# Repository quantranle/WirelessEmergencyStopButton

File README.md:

# Wireless Emergency Stop Button

by: Le Minh Quan Tran / Pham Duc Binh

**Faculty of Technology and Bionics**

***Rhine-Waal University of Applied Sciences***

Date: 13 January 2025

----

## Abstract

This project presents the design and implementation of a Wireless Emergency Stop Button (WESB)
 for enhancing safety in IoT applications, specifically the E-Go-Cart. 
 The WESB utilizes an ESP8266-based wireless communication link operating on a Wi-Fi network. 
 A mechanical button on the transmitter triggers an emergency stop signal, which is then transmitted 
 wirelessly to the receiver. The receiver is connected to the E-Go-Cart via a digital input/output interface. 
 Upon receiving the stop signal, the receiver initiates an emergency braking sequence implemented using MATLAB/Simulink, 
 bringing the E-Go-Cart to a safe halt within a defined distance. This system provides a reliable and efficient means 
 for remote emergency control of electric vehicles, improving overall safety and operational reliability.

## Table of Contents

[[_TOC_]]

## 1 Introduction

The increasing prevalence of electric vehicles (EVs), including those used in educational and recreational settings, 
demands robust safety mechanisms. This project addresses the need for a reliable and efficient emergency stop system for EVs,
 drawing inspiration from a real-world incident at Rhine-Waal University.

During a student festival, students were driving E-Go-Cart around campus under supervision. An accident occurred when a student, 
experiencing panic, lost control of their vehicle, potentially endangering pedestrians. Although the E-Go-Cart was equipped with 
an emergency stop button, the student's panicked state hindered their ability to react effectively. This incident underscored 
the limitations of traditional emergency stop mechanisms in high-stress situations and emphasized the need for a more robust and accessible solution.

Compared to traditional on-board emergency stop buttons, the WESB offers several advantages:

- Reduced Stress: Remote control eliminates the need for panicked individuals to locate and activate a specific button on the vehicle.
- Enhanced Accessibility: Integration with mobile applications provides convenient access to the emergency stop function.
- Centralized Control: The WESB allows for the simultaneous control of multiple vehicles, making it ideal for managing fleets or large-scale events.

This project seeks to address the shortcomings of existing safety measures and provide a more 
reliable and effective solution for ensuring the safe operation of electric vehicles in diverse settings.

## 2	Bill of Materials
| No. | Quality | Manufacturer               | Component               | Ordering code (manufacturer) | Vendor | Ordering code (vendor) | Price per unit (€) | Price (€)|
|:---:| :---:   | :---:                      | :---:                   | :---:                        | :---:  | :---:                  | :---:              | :---:    |
| 1   | 2       |                            | 2 AA cell holder        |                              | HSRW   |                        |                    |          |
| 2   | 1       |                            | PUSH BUTTON             |                              | HSRW   |                        |                    |          |
| 3   | 1       |                            | BUZZER                  |                              | HSRW   |                        |                    |          |
| 4   | 1       |                            | RED LED                 |                              | HSRW   |                        |                    |          |
| 5   | 1       |                            | GREEN LED               |                              | HSRW   |                        |                    |          |
| 6   | 1       |                            | POWER SWITCH            |                              | HSRW   |                        |                    |          |
| 7   | 1       | Diptronics                 | RESET BUTTON            |  DTSMF-32N-V-T/R             | Mouser | 113-DTSMF32NVTR        | 0.41               | 0.41     |
| 8   | 1       | Joy-IT                     | ESP8266                 | ESP8266-12F                  | Conrad | 1707668 - NA           | 4.19               | 4.19     |
| 9   | 1       | Semtech                    | RF Transceiver          | SX1268IMLTRT                 | Mouser | 947-SX1268IMLTRT       | 3.85               | 3.85     |
| 10  | 1       | Maxlinear                  | Voltage regulator       | SPX1117M3-L-3-3/TR           | Mouser | 701-SPX1117M3-L-33TR   | 0.49               | 0.49     |
| 11  | 1       | Silicon Laboratories       | USB Controller          | CP2102N-A02-GQFN28           | Mouser | 634-CP2102NA02GQFN28   | 3.28               | 3.28     |
| 12  | 1       | GlobalConnector Technology | Micro-usb header        | USB3140-30-0170-0-C          | Mouser | 640-USB31403001700C    | 0.75               | 0.75     |
| 13  | 1       | LPRS                       | RF Connector            | SMA CONNECTOR                | Mouser | 471-SMACONNECTOR       | 2.03               | 2.03     |
| 14  | 1       | Murata                     | RF Inductors - L1       | LQG15HS56NJ02D               | Mouser | 81-LQG15HS56NJ02D      | 0.09               | 0.09     |
| 15  | 1       | Murata                     | RF Inductors - L2       | LQG15HS8N2J02D               | Mouser | 81-LQG15HS8N2J02D      | 0.09               | 0.09     |
| 16  | 1       | Murata                     | RF Inductors - L3       | LQG15HN18NJ02D               | Mouser | 81-LQG15HN18NJ02D      | 0.09               | 0.09     |
| 17  | 1       | Murata                     | RF Inductors - L4       | LQW15AN33NH00D               | Mouser | 81-LQW15AN33NH00D      | 0.14               | 0.14     |
| 18  | 1       | TDK                        | Power Inductors - L5    | MLZ2012M150WT000             | Mouser | 810-MLZ2012M150WT000   | 0.11               | 0.11     |
| 19  | 1       | NDK                        | Crystals - Y1           | NX2016SA-32M-EXS00A-CS06465  | Mouser | 344-NX2016SA32S06465   | 0.52               | 0.52     |
| 20  | 1       |                            | Ceramic Capacitor - C1  |                              | HSRW   |                        |                    |          |
| 21  | 1       | KEMET                      | Ceramic Capacitor - C2  | C1206C475M4RACTU             | Mouser | 80-C1206C475M4R        | 0.88               | 0.88     | 
| 22  | 1       | KEMET                      | Ceramic Capacitor - C3  | C1206C475M4RACTU             | Mouser | 80-C1206C475M4R        | 0.88               | 0.88     | 
| 23  | 1       |                            | Ceramic Capacitor - C4  |                              | HSRW   |                        |                    |          | 
| 24  | 1       | KEMET                      | Ceramic Capacitor - C5  | C1206C475M4RACTU             | Mouser | 80-C1206C475M4R        | 0.88               | 0.88     |
| 25  | 1       |                            | Ceramic Capacitor - C6  |                              | HSRW   |                        |                    |          |
| 26  | 1       | Murata                     | Ceramic Capacitor - C7  | GRM155R71A474KE01D           | Mouser | 81-GRM155R71A474KE1D   | 0.36               | 0.36     |
| 27  | 1       | Murata                     | Ceramic Capacitor - C8  | GRM155R71C473KA01D           | Mouser | 81-GRM155R71C473KA01   | 0.09               | 0.09     |
| 28  | 1       | Murata                     | Ceramic Capacitor - C9  | GCM1555C1H820JA16D           | Mouser | 81-GCM1555C1H820JA6D   | 0.09               | 0.09     |
| 29  | 1       | Murata                     | Ceramic Capacitor - C10 | GJM1555C1H120JB01D           | Mouser | 81-GJM1555C1H120JB1D   | 0.12               | 0.12     |
| 30  | 1       | Murata                     | Ceramic Capacitor - C11 | GJM1555C1H3R6CB01D           | Mouser | 81-GJM1555C1H3R6CB1D   | 0.09               | 0.09     |
| 31  | 1       | Murata                     | Ceramic Capacitor - C12 | GJM1555C1H120JB01D           | Mouser | 81-GJM1555C1H120JB1D   | 0.12               | 0.12     |
| 32  | 1       | Murata                     | Ceramic Capacitor - C13 | GCM1555C1H101JA16D           | Mouser | 81-GCM1555C1H101JA6D   | 0.09               | 0.09     |
| 33  | 1       | Murata                     | Ceramic Capacitor - C14 | GJM1555C1H8R2CB01D           | Mouser | 81-GJM1555C1H8R2CB01   | 0.09               | 0.09     |
| 34  | 1       | Murata                     | Ceramic Capacitor - C15 | GJM1555C1H4R7CB01D           | Mouser | 81-GJM1555C1H4R7CB1D   | 0.09               | 0.09     |
| 35  | 1       | Murata                     | Ceramic Capacitor - C16 | GJM1555C1H3R9CB01D           | Mouser | 81-GJM1555C1H3R9CB1D   | 0.09               | 0.09     |
| 36  | 1       | Murata                     | Ceramic Capacitor - C17 | GJM1555C1H1R0BB01D           | Mouser | 81-GJM1555C1H1R0BB01   | 0.09               | 0.09     |
| 37  | 1       | Murata                     | Ceramic Capacitor - C18 | GCM1555C1H101JA16D           | Mouser | 81-GCM1555C1H101JA6D   | 0.09               | 0.09     |
| 38  | 1       | Murata                     | Ceramic Capacitor - C19 | GJM1555C1H120JB01D           | Mouser | 81-GJM1555C1H120JB1D   | 0.12               | 0.12     |
| 39  | 1       | Murata                     | Ceramic Capacitor - C20 | GJM1555C1H120JB01D           | Mouser | 81-GJM1555C1H120JB1D   | 0.12               | 0.12     |
| 40  | 3       | Littelfuse                 | TVS Diodes              | SP0503BAHTG                  | Mouser | 576-SP0503BAHTG        | 0.65               | 1.95     |
| 41  | 1       |                            | Resistor - R1           |                              | HSRW   |                        |                    |          |
| 42  | 1       |                            | Resistor - R2           |                              | HSRW   |                        |                    |          |
| 43  | 1       |                            | Resistor - R2           |                              | HSRW   |                        |                    |          |
| 44  | 1       |                            | Resistor - R4           |                              | HSRW   |                        |                    |          |
| 45  | 1       |                            | Resistor - R5           |                              | HSRW   |                        |                    |          |
| 46  | 1       |                            | Resistor - R6           |                              | HSRW   |                        |                    |          |
| 47  | 1       |                            | Resistor - R7           |                              | HSRW   |                        |                    |          |
| 48  | 1       |                            | Resistor - R8           |                              | HSRW   |                        |                    |          |
| 49  | 1       |                            | Resistor - R9           |                              | HSRW   |                        |                    |          |
| 50  | 1       |                            | Resistor - R10          |                              | HSRW   |                        |                    |          |
| 51  | 1       | Vishay                     | Resistor - R11          | CRCW04020000Z0ED             | Mouser | 71-CRCW0402-0-E3       | 0.09               | 0.09     |
| 52  | 2       |                            | 1x02 PIN HEADER         |                              | HSRW   |                        |                    |          |
| 53  | 2       |                            | 1x08 PIN HEADER         |                              | HSRW   |                        |                    |          |

## 3	Methodology

### 3.1     Schematic
Final Schematic:

 Figure 1: Schematic

### 3.2     PCB Design
Final PCB:

 Figure 2: PCB design

### 3.3     Prototyping

### 3.4     Assembly Process

#### 3.4.1 Soldering SMD components
First step: Use a stencil and apply solder paste to PCB.

 Figure 3: Using a stencil

After applying solder paste, pick up all SMD components and make sure they are all in correct place.

 Figure 4: Put on SMD components

Next, put PCB into the oven then bake it. The setup was supported by Mr. Muh.

 Figure 5: Put PCB into the Oven

 Figure 6: Baking PCB

Last but not least, test the connectivity of the SMD components with the multimeter.

#### 3.4.2 Soldering THT components
Solder THT components with Solder pen.

 Figure 7: Solder THT components

Same as SMD components, make sure all THT components are connected appropriately.

## 4    Programming and uploading firmware
We programmed the ESP8266 chips using Arduino IDE and PlatformIO.  
The files of Transmitter and Receiver are in the ***code/Official code*** folder.

## 5    Troubleshooting
**[1]**
Can power the ESP8266 by USB cable, but not able to program. The device manager from the laptop cannot detect the USB port, although
download a correct driver.

**[2]**
Able to prototype LoRa module, but difficult to implement in the project. There have to be hard-work programming and deep understand in
RF functions.

**[3]**
Able to program the ESP8266 chips by using FDTI FT232RL Module. However, when the ESP8266 chips were soldered to the PCB, we could not
program them by using FDTI module anymore.

## 6	Results
This is the result:
 Figure 8: Final Products

## 7	Power Consumption and Battery Life
**Power Consumption**  
V_supply = 6V (measured)  
I_output = 200mA (measured)  
⇒ P_consumed = V_supply * I_output = 5.5V * 200mA = 1200 mW.  
**P_consumed = 1200 mW**  

**Battery Life**  
Battery capacity of AAA Alkaline: 1200 mAh (datasheet)  
Battery Life = 1200mAh / 200mA = **6 hours**

## 8	Further Improvements
- **Integration with Other Devices:** Integrate wireless e-stops with other E-Carts or Robots to create a comprehensive safety network.
- **Further Program Development:** Sleep mode to optimize the battery life
- **Application of The Lora Module** to increase distance and reliable communication. 
- **Ergonomic Design:** Ensure ergonomic design for comfortable and intuitive operation (Push button, battery level, signal strength,…)

## 9	References

* [1] ESP32 with LoRa using Arduino IDE – Getting Started (https://randomnerdtutorials.com/esp32-lora-rfm95-transceiver-arduino-ide/)
* [2] CP2102N (https://www.mouser.de/datasheet/2/368/cp2102n_datasheet-1634912.pdf)
* [3] ESP-12E WiFi Module (https://components101.com/sites/default/files/2021-09/ESP12E-Datasheet.pdf)
* [4] ESP8266 - Button - Piezo Buzzer (https://newbiely.com/tutorials/esp8266/esp8266-button-piezo-buzzer)
* [5] Configure an ESP8266 as a WiFi Access Point
* [6] CP2102N Driver (https://www.silabs.com/developer-tools/usb-to-uart-bridge-vcp-drivers?tab=overview)
* [7] Best battery for ESP32 (https://diyi0t.com/best-battery-for-esp32-nodemcu/)
* [8] Tips for ESP8266 (https://www.instructables.com/ESP8266-Pro-Tips/)
* [9] Electronic Component Search Engine (https://componentsearchengine.com/)

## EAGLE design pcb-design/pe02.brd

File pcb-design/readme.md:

# PCB design

 Figure 1: ESP8266 PCB design

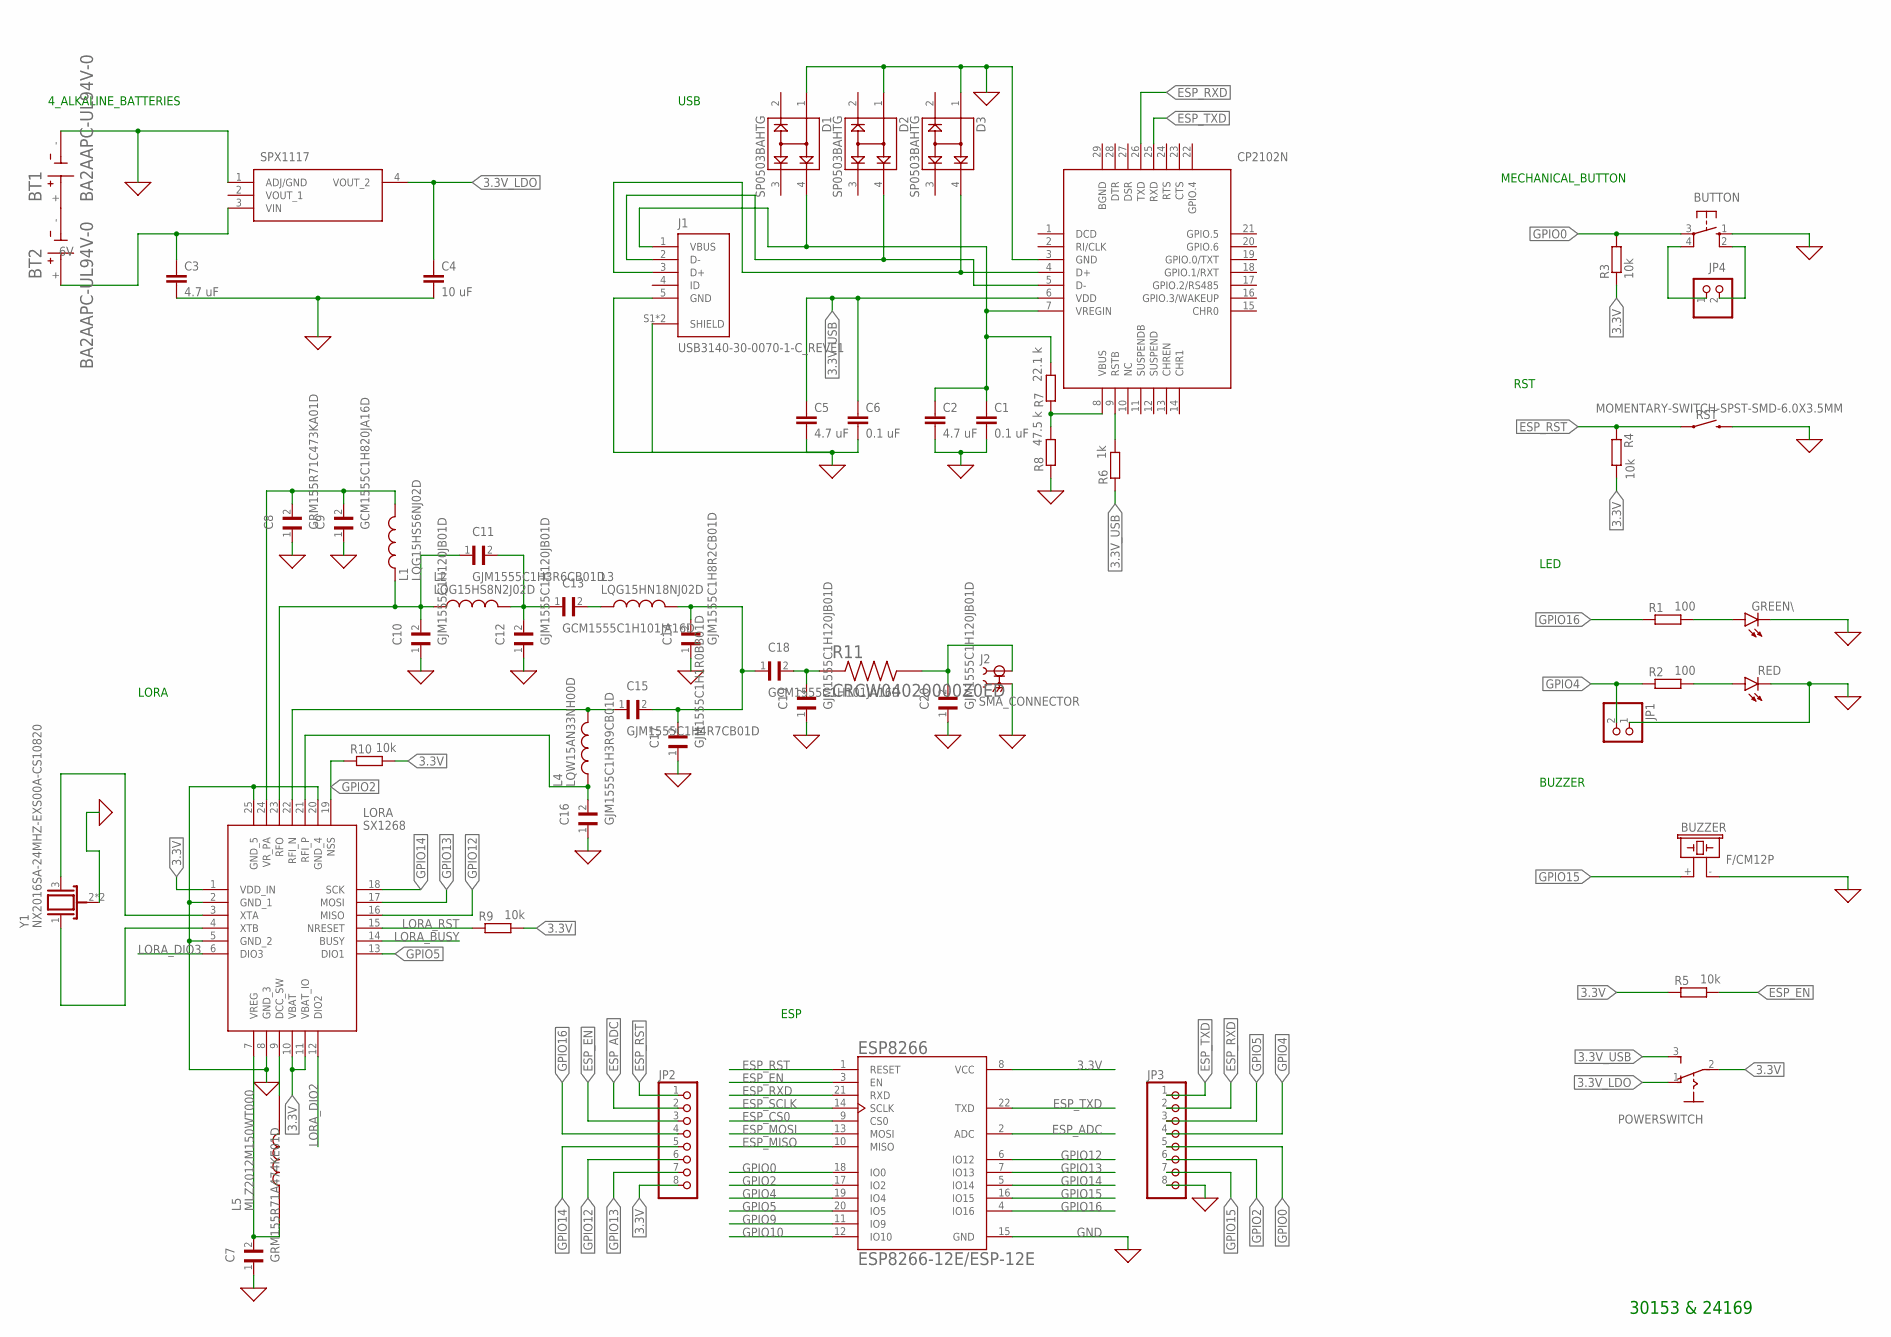
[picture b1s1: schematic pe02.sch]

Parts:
BT1, BT2: BA2AAPC-UL94V-0; BAT_BA2AAPC-UL94V-0
BUTTON: 10-XX; B3F-10XX
BUZZER: F/CM12P
C1, C6: 0.1 uF; C1206K
C2, C3, C5: 4.7 uF; C1206K
C4: 10 uF; C1206K
C7: GRM155R71A474KE01D; CAPC1005X55N
C8: GRM155R71C473KA01D; CAPC1005X55N
C9: GCM1555C1H820JA16D; CAPC1005X55N
C10, C12, C19, C20: GJM1555C1H120JB01D; CAPC1005X55N
C11: GJM1555C1H3R6CB01D; CAPC1005X55N
C13, C18: GCM1555C1H101JA16D; CAPC1005X55N
C14: GJM1555C1H8R2CB01D; CAPC1005X55N
C15: GJM1555C1H4R7CB01D; CAPC1005X55N
C16: GJM1555C1H3R9CB01D; CAPC1005X55N
C17: GJM1555C1H1R0BB01D; CAPC1005X55N
CP2102N: CP2102N-A02-GQFN28; QFN50P500X500X80-29N
D1, D2, D3: SP0503BAHTG; SOT143
ESP8266: ESP8266-12E/ESP-12E; XCVR_ESP8266-12E/ESP-12E
GREEN\: LEDCHIPLED_1206; CHIPLED_1206
J1: USB3140-30-0070-1-C_REVE1; GCT_USB3140-30-0070-1-C_REVE1
J2: SMA_CONNECTOR; LPRS_SMA_CONNECTOR
JP1, JP4: PINHD-1X2; 1X02
JP2, JP3: PINHD-1X8; 1X08
L1: LQG15HS56NJ02D; INDC1005X55N
L2: LQG15HS8N2J02D; INDC1005X55N
L3: LQG15HN18NJ02D; INDC1005X55N
L4: LQW15AN33NH00D; INDC1005X60N
L5: MLZ2012M150WT000; INDC2012X145N
LORA: SX1268; QFN50P400X400X100-25N
POWERSWITCH: 255SB
R1, R2: 100; R1206
R3, R4, R5, R9, R10: 10k; R1206
R6: 1k; R1206
R7: 22.1 k; R1206
R8: 47.5 k; R1206
R11: CRCW04020000Z0ED; RESC1005X40N
RED: LEDCHIPLED_1206; CHIPLED_1206
RST: MOMENTARY-SWITCH-SPST-SMD-6.0X3.5MM; TACTILE_SWITCH_SMD_6.0X3.5MM
SPX1117: SPX1117M3-L-3-3_TR; SOT230P700X180-4N
Y1: NX2016SA-24MHZ-EXS00A-CS10820; OSC_NX2016SA-24MHZ-EXS00A-CS10820

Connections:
3.3V: ESP8266.8 (VCC), JP2.8, LORA.1 (VDD_IN), LORA.10 (VBAT), LORA.11 (VBAT_IO), POWERSWITCH.2, R3.1, R4.2, R5.1, R9.2, R10.2
3.3V_LDO: C4.1, POWERSWITCH.1 (O), SPX1117.4 (VOUT_2)
3.3V_USB: C5.1, C6.1, CP2102N.6 (VDD), POWERSWITCH.3 (S), R6.1
6V: BT2.+, C3.1, SPX1117.3 (VIN)
BGND: CP2102N.29 (BGND)
ESP_ADC: ESP8266.2 (ADC), JP2.2
ESP_CS0: ESP8266.9 (CS0)
ESP_EN: ESP8266.3 (EN), JP2.3, R5.2
ESP_MISO: ESP8266.10 (MISO)
ESP_MOSI: ESP8266.13 (MOSI)
ESP_RST: ESP8266.1 (RESET), JP2.1, R4.1, RST.1
ESP_RXD: CP2102N.26 (TXD), ESP8266.21 (RXD), JP3.2
ESP_SCLK: ESP8266.14 (SCLK)
ESP_TXD: CP2102N.25 (RXD), ESP8266.22 (TXD), JP3.1
GND: BT1.-, BUTTON.1 (S), BUZZER.- (2), C1.2, C2.2, C3.2, C4.2, C5.2, C6.2, C7.1, C8.1, C9.1, C10.1, C12.1, C14.1, C16.1, C17.1, C19.1, C20.1, CP2102N.3 (GND), D1.1, D2.1, D3.1, ESP8266.15 (GND), GREEN\.C, J1.5 (GND), J1.S1 (SHIELD), J1.S2 (SHIELD), J2.G1 (2), J2.G2 (2), J2.G3 (2), J2.G4 (2), JP1.1, JP3.8, LORA.2 (GND_1), LORA.5 (GND_2), LORA.8 (GND_3), LORA.20 (GND_4), LORA.25 (GND_5), R8.1, RED.C, RST.2, SPX1117.1 (ADJ/GND), Y1.2 (GND), Y1.4 (GND)
GPIO0: BUTTON.3, ESP8266.18 (IO0), JP3.5, R3.2
GPIO2: ESP8266.17 (IO2), JP3.6, LORA.19 (NSS), R10.1
GPIO4: ESP8266.19 (IO4), JP1.2, JP3.4, R2.1
GPIO5: ESP8266.20 (IO5), JP3.3, LORA.13 (DIO1)
GPIO9: ESP8266.11 (IO9)
GPIO10: ESP8266.12 (IO10)
GPIO12: ESP8266.6 (IO12), JP2.6, LORA.16 (MISO)
GPIO13: ESP8266.7 (IO13), JP2.7, LORA.17 (MOSI)
GPIO14: ESP8266.5 (IO14), JP2.5, LORA.18 (SCK)
GPIO15: BUZZER.+ (1), ESP8266.16 (IO15), JP3.7
GPIO16: ESP8266.4 (IO16), JP2.4, R1.1
LORA_BUSY: LORA.14 (BUSY)
LORA_DIO2: LORA.12 (DIO2)
LORA_DIO3: LORA.6 (DIO3)
LORA_RFI_N: C15.1, L4.2, LORA.22 (RFI_N)
LORA_RFI_P: C16.2, L4.1, LORA.21 (RFI_P)
LORA_RFO: C10.2, C11.1, L1.1, L2.1, LORA.23 (RFO)
LORA_RST: LORA.15 (NRESET), R9.1
LORA_VR_PA: C8.2, C9.2, L1.2, LORA.24 (VR_PA)
LORA_XTA: LORA.3 (XTA), Y1.3
LORA_XTB: LORA.4 (XTB), Y1.1
unnamed: BUTTON.4 (P1), JP4.1
unnamed: BUTTON.2 (S1), JP4.2
unnamed: C7.2, L5.1, LORA.7 (VREG)
unnamed: L5.2, LORA.9 (DCC_SW)
unnamed: CP2102N.5 (D-), D2.4, J1.2 (D-)
unnamed: C13.2, L3.1
unnamed: GREEN\.A, R1.2
unnamed: R2.2, RED.A
unnamed: C11.2, C12.2, C13.1, L2.2
unnamed: BT1.+, BT2.-
unnamed: C14.2, C15.2, C17.2, C18.1, L3.2
unnamed: C20.2, J2.1, R11.2
unnamed: C18.2, C19.2, R11.1
unnamed: CP2102N.4 (D+), D3.4, J1.3 (D+)
unnamed: CP2102N.9 (RSTB), R6.2
unnamed: CP2102N.8 (VBUS), R7.1, R8.2
unnamed: C1.1, C2.1, CP2102N.7 (VREGIN), D1.4, J1.1 (VBUS), R7.2

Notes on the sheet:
MECHANICAL_BUTTON
4_ALKALINE_BATTERIES
LORA
USB
30153 & 24169
RST
LED
BUZZER
ESP

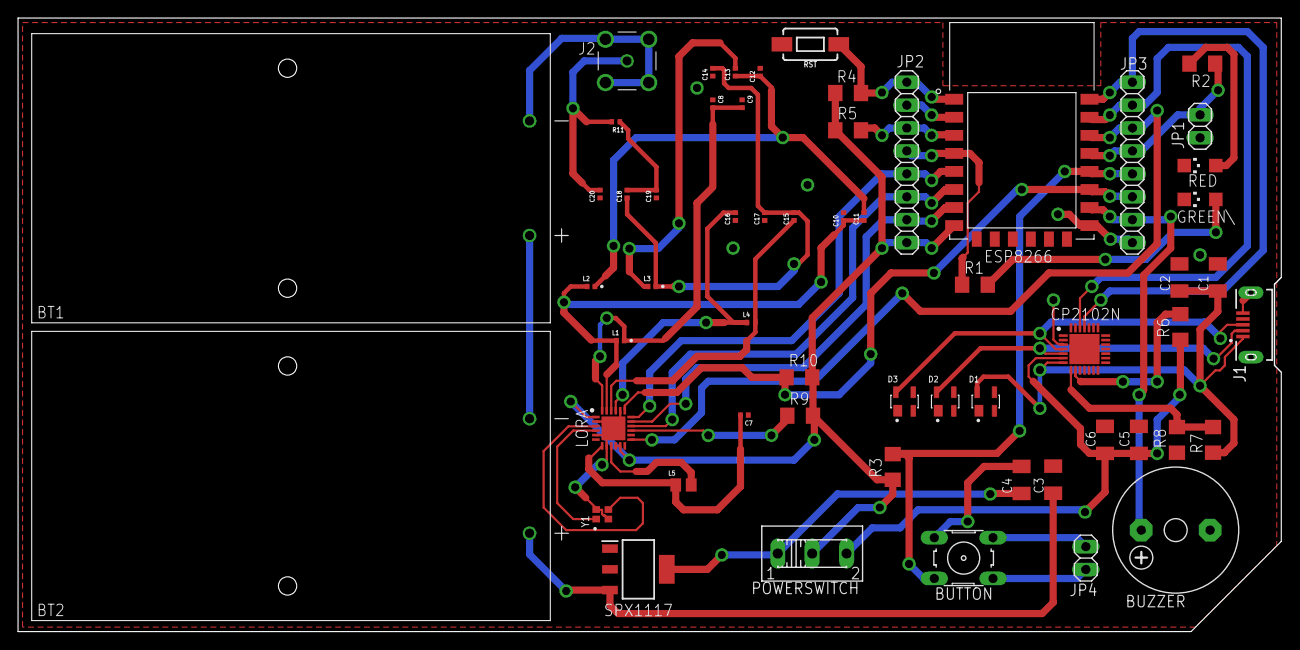
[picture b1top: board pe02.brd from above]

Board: 2 copper layers, 139.9 x 67.8 mm, 58 parts (0 on the bottom side), 43 nets.

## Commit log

2025-02-15 PE project

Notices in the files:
parts and their libraries:
SparkFun-Switches: Licensing: Creative Commons ShareAlike 4.0 International - https://creativecommons.org/licenses/by-sa/4.0
